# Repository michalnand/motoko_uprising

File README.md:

# Motoko Uprising
## line following robot with neural network predictor

Advanced line following robot, using custom deep neural network for curve shape prediction.
Robot can recognize straight line and speed up.

* Video1 of woking robot [motoko video 1](https://www.youtube.com/watch?v=E9FJIDowNmU)
* Video2 of woking robot [motoko video 2](https://www.youtube.com/watch?v=xUAJ1LA6Xwc)

## hardware

* CPU is ARM Cortex M4F, stm32f303, 72MHz
  * with simd instructions, good to have for deep learning
* gyroscope : lsm303 
  * (or something like THAT - yeah, they are changing it more often then socks)
* motors : pololu HP 1:30, micro metal gear, with magnetic encoders
* motor driver : TI DRV8834
* line sensors : phototransitors for visible light (not IR)
  * Iam using white leds, so the line can be colored - not only black
* obstacle detection :
  * common IR leds, and laser (still not working as I wish - too slow, but high range)
* accu : LiPol 2S, 150mAh, from dualsky

Some photos from mounting this devilry device :
* PCB design are in  [pcb](hardware/export), ready to send to your favorite manufactor
  * 
  * 
  * 
  * 
  
* Chassis, there are little of 3D printed parts [3d print](hardware/chassis)
  * 

## firmware

### control loops

* ADC reads line sensor, using quadratic interpolation for precission line position estimation
* for steering PD controller is used
* for motor controll two PIDs are used (data from encoders are filtered by low pass filters)
* target speed is estimated by neural network, using line shape classification

### neural network

tiny convolutional neural network is used, with architecture :
IN1x8x8 - C4x3x3 - P2x2 - C8x3x3 - P2x2 - FC5

the custom embedded CNN framework is used

```cpp
LineNetwork::LineNetwork()
			:EmbeddedNet()
{
  input_shape.w = 8;
  input_shape.h = 8;
  input_shape.d = 1;

  output_shape.w = 1;
  output_shape.h = 1; 
  output_shape.d = 5;

  layers[0] = new EmbeddedNetConvolutionLayer(layer_0_shape,layer_0_input_shape,layer_0_output_shape,layer_0_weights,layer_0_bias,layer_0_weights_range,layer_0_bias_range);
  layers[1] = new EmbeddedNetMaxPoolingLayer(layer_1_shape,layer_1_input_shape,layer_1_output_shape);
  layers[2] = new EmbeddedNetConvolutionLayer(layer_2_shape,layer_2_input_shape,layer_2_output_shape,layer_2_weights,layer_2_bias,layer_2_weights_range,layer_2_bias_range);
  layers[3] = new EmbeddedNetMaxPoolingLayer(layer_3_shape,layer_3_input_shape,layer_3_output_shape);
  layers[4] = new EmbeddedNetFcLayer(layer_4_shape,layer_4_input_shape,layer_4_output_shape,layer_4_weights,layer_4_bias,layer_4_weights_range,layer_4_bias_range);

  layers_count = 5;
  allocate_buffer();
}
```

### PIDs

PIDs in differential form are used, with antiwindup and derivation kick avoid trick

the controller equation is :
%20%3D%20u(n-1)%20%2B%20k_0e(n)%20%2B%20k_1e(n-1)%20%2B%20k_2e(n-2))

where
* e(n) is error
* u(n) is controller output
* k0 = kp + ki + kd
* k1 = -kp     -2kd
* k2 = kd

```cpp
float PID::process(float error, float plant_output)
{
    e1 = e0;
    e0 = error;

    x2 = x1;
    x1 = x0;
    x0 = plant_output;

    u+= k0*e0 + k1*e1 - kd*(x0 - 2*x1 + x2);

    if (u > limit)
      u = limit;

    if (u < -limit)
      u = -limit;

    return u;
}
```

motors controllers step response :

## debug application

There is debug application written in Python. Data received from robot are visualised in custom GUI written
using OpenGL. Data are transfered in JSON format.

Robot GUI is also designed in json - to modify gui design, only this file need to be modified. Example of gui.json file format : 

```json
"widgets" :
  {
    "type"      : "label",
    "position"  : [0.0, 0.0, 0.0],
    "color"     : [1.0, 0.0, 0.0],
    "font_size" : 0.1,

    "widgets" : [
                  {
                    "type"           : "bar_graph",
                    "position"       : [-2.0, 1.25, 0.0],
                    "color"          : [0.5, 1.0, 0.0],
                    "bar_color"      : [0.8, 0.8, 0.8],

                    "font_size" : 0.05,

                    "width"     : 1.5,
                    "height"    : 0.5,

                    "filled"    : false,
                    "enlight_max_value" : false,

                    "frame_width" : 0.01,
                    "label"     : "LINE SENSORS",

                    "min_value" : 0.0,
                    "max_value" : 1024.0,

                    "variable"  : {
                                    "name"  : "line_sensors",
                                    "value" : [3, 40, 500, 1000, 700, 50, 0, 0]
                                  }
                  },
...
```

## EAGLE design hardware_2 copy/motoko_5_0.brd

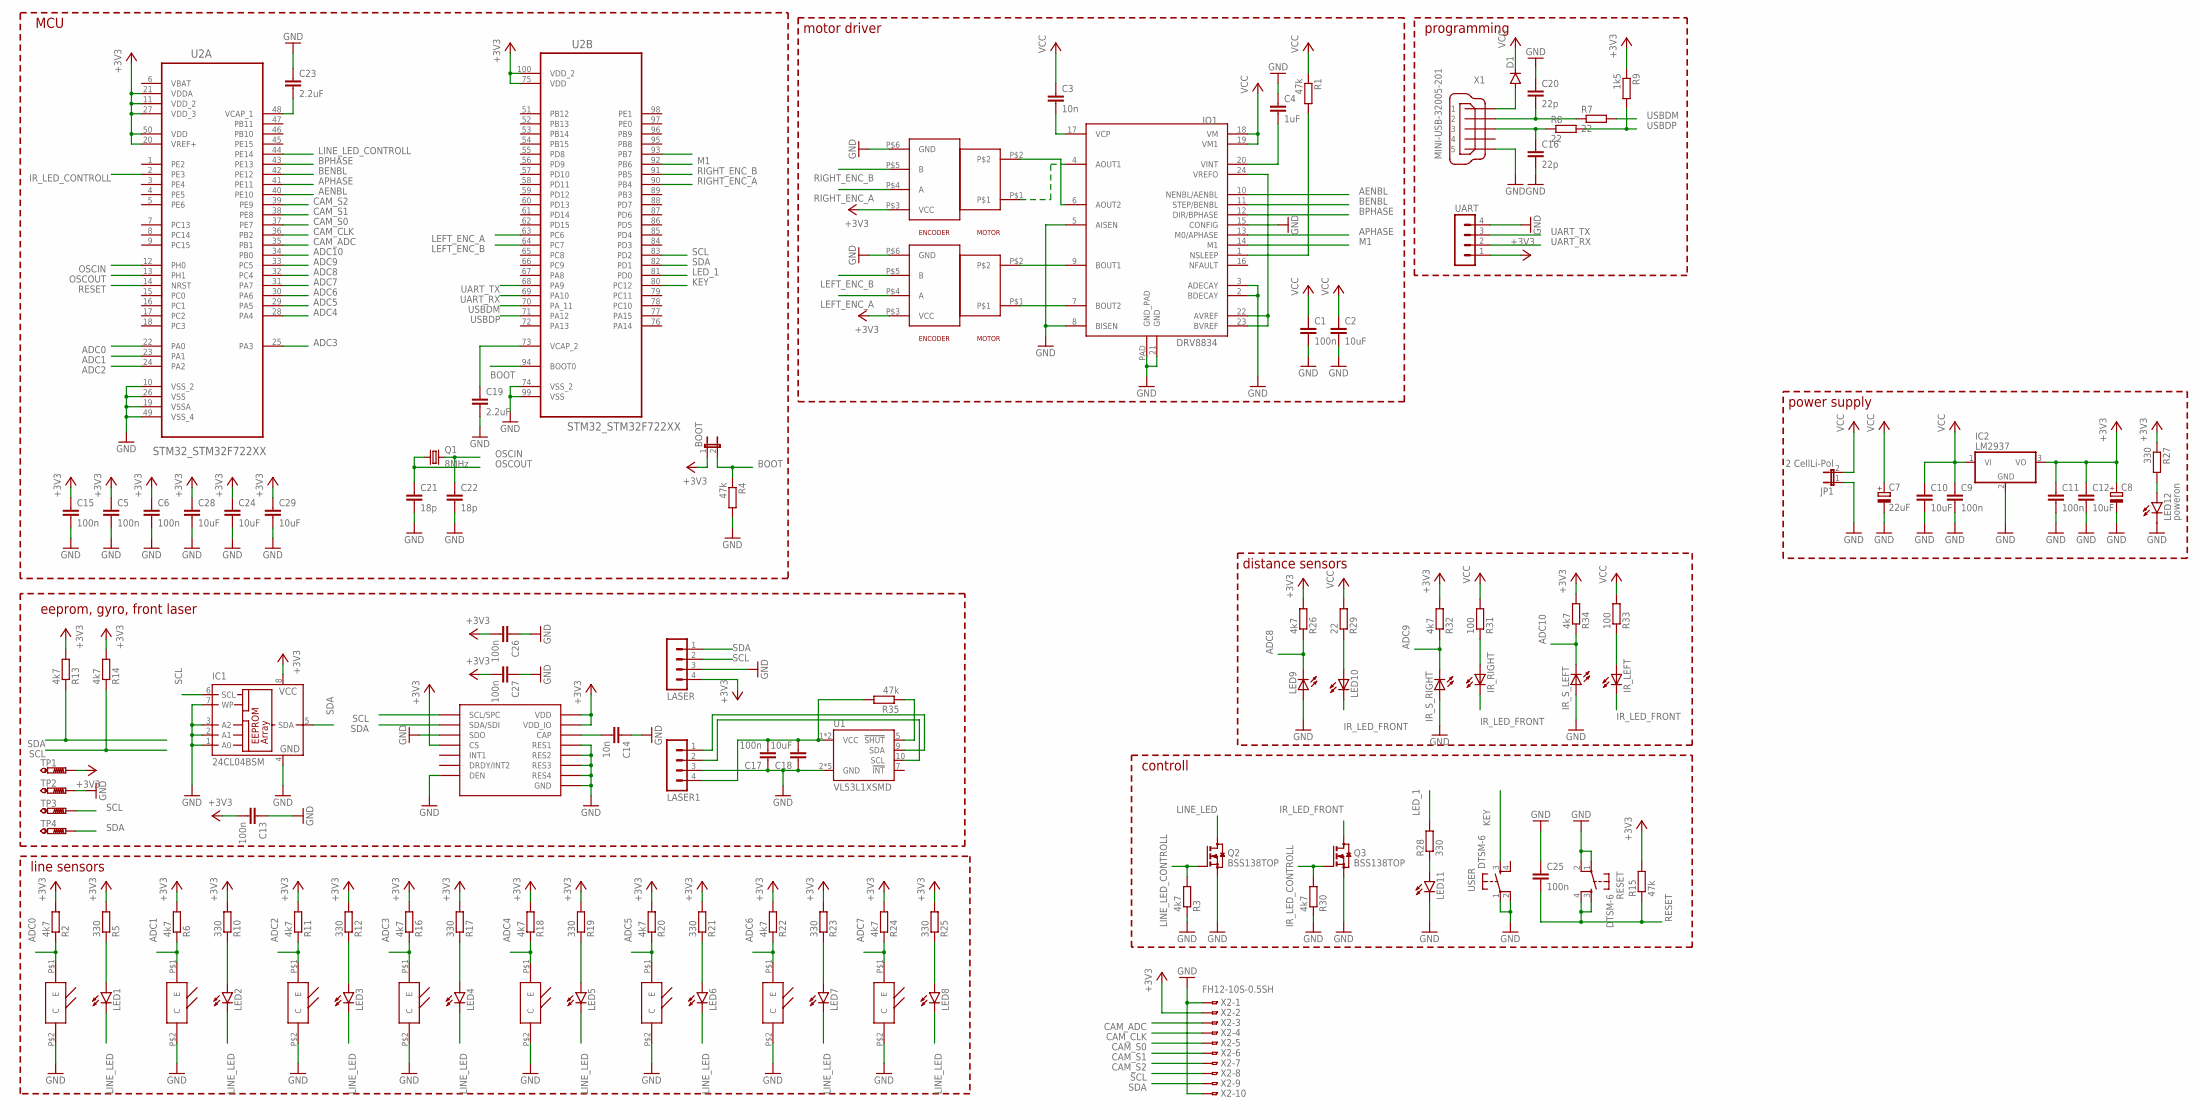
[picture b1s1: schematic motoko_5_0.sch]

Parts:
BOOT: JP1E; JP1
C1: 100n; C1206
C2: 10uF; C1206
C3: 10n; C1206
C4: 1uF; C1206
C5, C6, C9, C11, C13, C15, C17, C25, C26, C27: 100n; C0805
C7: 22uF; 153CLV-0505
C8: CPOL-EU140CLH-1010; 140CLH-1010
C10, C12, C18, C24, C28, C29: 10uF; C0805
C14: 10n; C0805
C16, C20: 22p; C0805
C19, C23: 2.2uF; C0805
C21, C22: 18p; C0805
D1: DIODE-SMB; SMB
IC1: 24CL04BSM; SO-08M
IC2: LM2937; TO263-3
IO1: DRV8834; DRV8834_PCK
IR_LEFT: LED5MM
IR_RIGHT: LED5MM
IR_S_LEFT: LED5MM
IR_S_RIGHT: LED5MM
JP1: 2 CellLi-Pol; JP1
LASER, LASER1: MA04-1
LED1, LED2, LED3, LED4, LED5, LED6, LED7, LED8, LED11: LEDCHIPLED_1206; CHIPLED_1206
LED9, LED10: LED5MM
LED12: poweron; CHIPLED_1206
LSM6DS0: ST_L3GD20H; ST_LGA16L
Q1: 8MHz; CTS406
Q2, Q3: BSS138TOP; SOT23
R1: 47k; M1206
R2, R3, R6, R11, R13, R14, R16, R18, R20, R22, R24, R26, R30, R32, R34: 4k7; M0805
R4, R15, R35: 47k; M0805
R5, R10, R12, R17, R19, R21, R23, R25, R27, R28: 330; M0805
R7, R8, R29: 22; M0805
R9: 1k5; M0805
R31, R33: 100; M0805
RESET: DTSM-6
TP1, TP2, TP3, TP4: PTR1B1,27; B1,27
U1: VL53L1XSMD; VL53L1X
U2: STM32_STM32F722XX; STM32_QFP50P1600X1600X160-100N
U$3, U$4, U$5, U$6, U$7, U$8, U$9, U$10: SFH3710
U$11, U$12: POLOLU_GEAR_MOTORPOLO; POLOLU_GEAR_MOTOR
UART: MA04-1
USER: DTSM-6
X1: MINI-USB-32005-201; 32005-201
X2: FH12-10S-0.5SH

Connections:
+3V3: BOOT.1, C5.1, C6.1, C8.+, C11.1, C12.1, C13.2, C15.1, C24.1, C26.2, C27.2, C28.1, C29.1, IC1.8 (VCC), IC2.3 (VO), LASER.4, LSM6DS0.P$1 (VDD_IO), LSM6DS0.P$5 (CS), LSM6DS0.P$16 (VDD), R2.2, R5.2, R6.2, R9.1, R10.2, R11.2, R12.2, R13.2, R14.2, R15.2, R16.2, R17.2, R18.2, R19.2, R20.2, R21.2, R22.2, R23.2, R24.2, R25.2, R26.2, R27.1, R32.2, R34.2, TP1.TP, U2.11 (VDD_2), U2.20 (VREF+), U2.21 (VDDA), U2.27 (VDD_3), U2.50 (VDD), U2.75 (VDD), U2.100 (VDD_2), U$11.P$3 (VCC), U$12.P$3 (VCC), UART.1, X2.2
ADC0: R2.1, U2.22 (PA0), U$3.P$1 (E)
ADC1: R6.1, U2.23 (PA1), U$4.P$1 (E)
ADC2: R11.1, U2.24 (PA2), U$5.P$1 (E)
ADC3: R16.1, U2.25 (PA3), U$6.P$1 (E)
ADC4: R18.1, U2.28 (PA4), U$7.P$1 (E)
ADC5: R20.1, U2.29 (PA5), U$8.P$1 (E)
ADC6: R22.1, U2.30 (PA6), U$9.P$1 (E)
ADC7: R24.1, U2.31 (PA7), U$10.P$1 (E)
ADC8: LED9.K (C), R26.1, U2.32 (PC4)
ADC9: IR_S_RIGHT.K (C), R32.1, U2.33 (PC5)
ADC10: IR_S_LEFT.K (C), R34.1, U2.34 (PB0)
AENBL: IO1.10 (NENBL/AENBL), U2.40 (PE10)
APHASE: IO1.13 (M0/APHASE), U2.41 (PE11)
BENBL: IO1.11 (STEP/BENBL), U2.42 (PE12)
BOOT: BOOT.2, R4.1, U2.94 (BOOT0)
BPHASE: IO1.12 (DIR/BPHASE), U2.43 (PE13)
CAM_ADC: U2.35 (PB1), X2.3
CAM_CLK: U2.36 (PB2), X2.4
CAM_S0: U2.37 (PE7), X2.5
CAM_S1: U2.38 (PE8), X2.6
CAM_S2: U2.39 (PE9), X2.7
GND: C1.2, C2.2, C4.1, C5.2, C6.2, C7.-, C8.-, C9.2, C10.2, C11.2, C12.2, C13.1, C14.1, C15.2, C16.2, C17.1, C18.1, C19.2, C20.1, C21.2, C22.2, C23.1, C24.2, C25.1, C26.1, C27.1, C28.2, C29.2, IC1.1 (A0), IC1.2 (A1), IC1.3 (A2), IC1.4 (GND), IC1.7 (WP), IC2.2 (GND), IO1.2 (BDECAY), IO1.3 (ADECAY), IO1.5 (AISEN), IO1.8 (BISEN), IO1.15 (CONFIG), IO1.21 (GND), IO1.PAD (GND_PAD), IR_S_LEFT.A, IR_S_RIGHT.A, JP1.1, LASER.3, LASER1.3, LED9.A, LED11.C, LED12.C, LSM6DS0.P$4 (SDO), LSM6DS0.P$8 (DEN), LSM6DS0.P$9 (RES1), LSM6DS0.P$10 (RES2), LSM6DS0.P$11 (RES3), LSM6DS0.P$12 (GND), LSM6DS0.P$13 (GND), LSM6DS0.P$15 (RES4), Q2.2 (S), Q3.2 (S), R3.1, R4.2, R30.1, RESET.1, RESET.2, TP2.TP, U1.2 (GND), U1.3 (GND), U1.4 (GND), U1.6 (GND), U1.12 (GND), U2.10 (VSS_2), U2.19 (VSSA), U2.26 (VSS), U2.49 (VSS_4), U2.74 (VSS_2), U2.99 (VSS), U$3.P$2 (C), U$4.P$2 (C), U$5.P$2 (C), U$6.P$2 (C), U$7.P$2 (C), U$8.P$2 (C), U$9.P$2 (C), U$10.P$2 (C), U$11.P$6 (GND), U$12.P$6 (GND), UART.4, USER.1, USER.2, X1.5, X2.1, X2.10
IR_LED_CONTROLL: Q3.1 (G), R30.2, U2.2 (PE3)
IR_LED_FRONT: IR_LEFT.K (C), IR_RIGHT.K (C), LED10.K (C), Q3.3 (D)
KEY: U2.80 (PC12), USER.3
LED_1: R28.2, U2.81 (PD0)
LEFT_ENC_A: U2.63 (PC6), U$11.P$4 (A)
LEFT_ENC_B: U2.64 (PC7), U$11.P$5 (B)
LINE_LED: LED1.C, LED2.C, LED3.C, LED4.C, LED5.C, LED6.C, LED7.C, LED8.C, Q2.3 (D)
LINE_LED_CONTROLL: Q2.1 (G), R3.2, U2.44 (PE14)
M1: IO1.14 (M1), U2.92 (PB6)
unnamed: IO1.6 (AOUT2), U$12.P$2
unnamed: IO1.4 (AOUT1), U$12.P$1
unnamed: IO1.7 (BOUT2), U$11.P$1
unnamed: IO1.9 (BOUT1), U$11.P$2
unnamed: C3.2, IO1.17 (VCP)
unnamed: C14.2, LSM6DS0.P$14 (CAP)
unnamed: LED10.A, R29.1
unnamed: IO1.22 (AVREF), IO1.23 (BVREF), IO1.24 (VREFO)
unnamed: IO1.1 (NSLEEP), R1.2
unnamed: IR_LEFT.A, R33.1
unnamed: LED1.A, R5.1
unnamed: LED2.A, R10.1
unnamed: LED3.A, R12.1
unnamed: LED4.A, R17.1
unnamed: LED5.A, R19.1
unnamed: LED6.A, R21.1
unnamed: LED7.A, R23.1
unnamed: LED8.A, R25.1
unnamed: C4.2, IO1.20 (VINT)
unnamed: LED12.A, R27.2
unnamed: IR_RIGHT.A, R31.1
unnamed: C19.1, U2.73 (VCAP_2)
unnamed: C17.2, C18.2, LASER1.4, R35.2, U1.1 (VCC), U1.11 (VCC)
unnamed: LASER1.1, U1.9 (SDA)
unnamed: LASER1.2, U1.10 (SCL)
unnamed: R35.1, U1.5 (!SHUT)
unnamed: C23.2, U2.48 (VCAP_1)
unnamed: LED11.A, R28.1
unnamed: C20.2, R7.1, X1.2
unnamed: C16.1, R8.1, X1.3
unnamed: D1.A, X1.1
OSCIN: C22.1, Q1.3 (2), U2.12 (PH0)
OSCOUT: C21.1, Q1.1, U2.13 (PH1)
RESET: C25.2, R15.1, RESET.3, RESET.4, U2.14 (NRST)
RIGHT_ENC_A: U2.90 (PB4), U$12.P$4 (A)
RIGHT_ENC_B: U2.91 (PB5), U$12.P$5 (B)
SCL: IC1.6 (SCL), LASER.2, LSM6DS0.P$2 (SCL/SPC), R14.1, TP3.TP, U2.83 (PD2), X2.8
SDA: IC1.5 (SDA), LASER.1, LSM6DS0.P$3 (SDA/SDI), R13.1, TP4.TP, U2.82 (PD1), X2.9
UART_RX: U2.69 (PA10), UART.2
UART_TX: U2.68 (PA9), UART.3
USBDM: R7.2, U2.70 (PA_11)
USBDP: R8.2, R9.2, U2.71 (PA12)
VBAT: U2.6 (VBAT)
VCC: C1.1, C2.1, C3.1, C7.+, C9.1, C10.1, D1.C, IC2.1 (VI), IO1.18 (VM), IO1.19 (VM1), JP1.2, R1.1, R29.2, R31.2, R33.2

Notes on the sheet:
power supply
line sensors
programming
MCU
motor driver
distance sensors
controll
eeprom, gyro, front laser

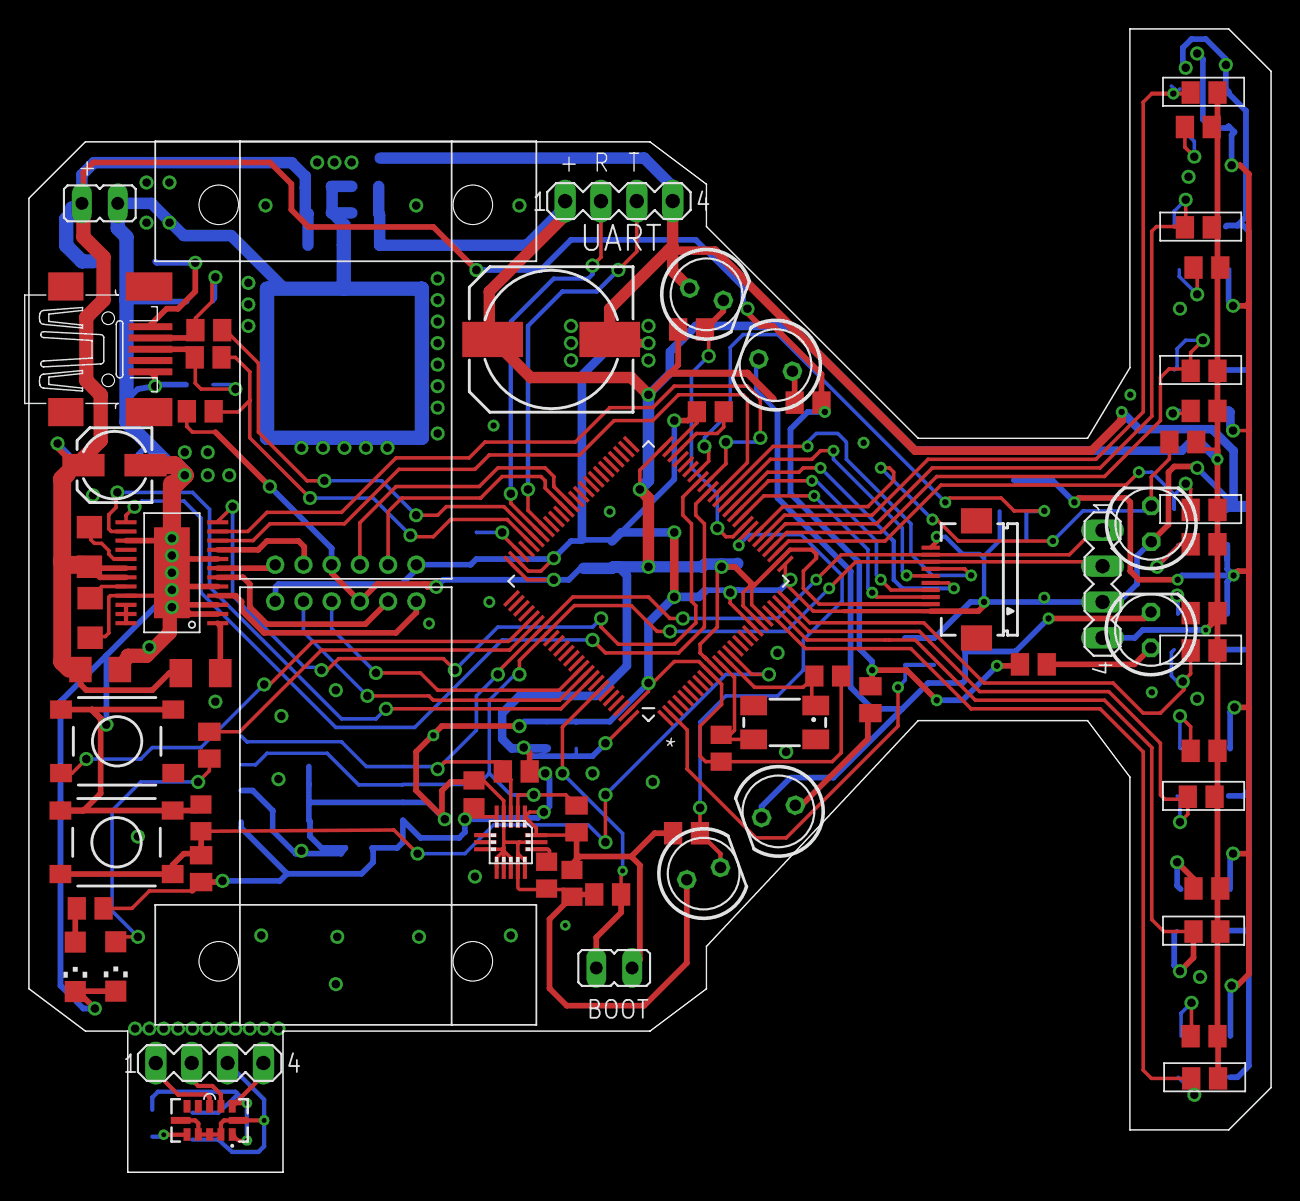
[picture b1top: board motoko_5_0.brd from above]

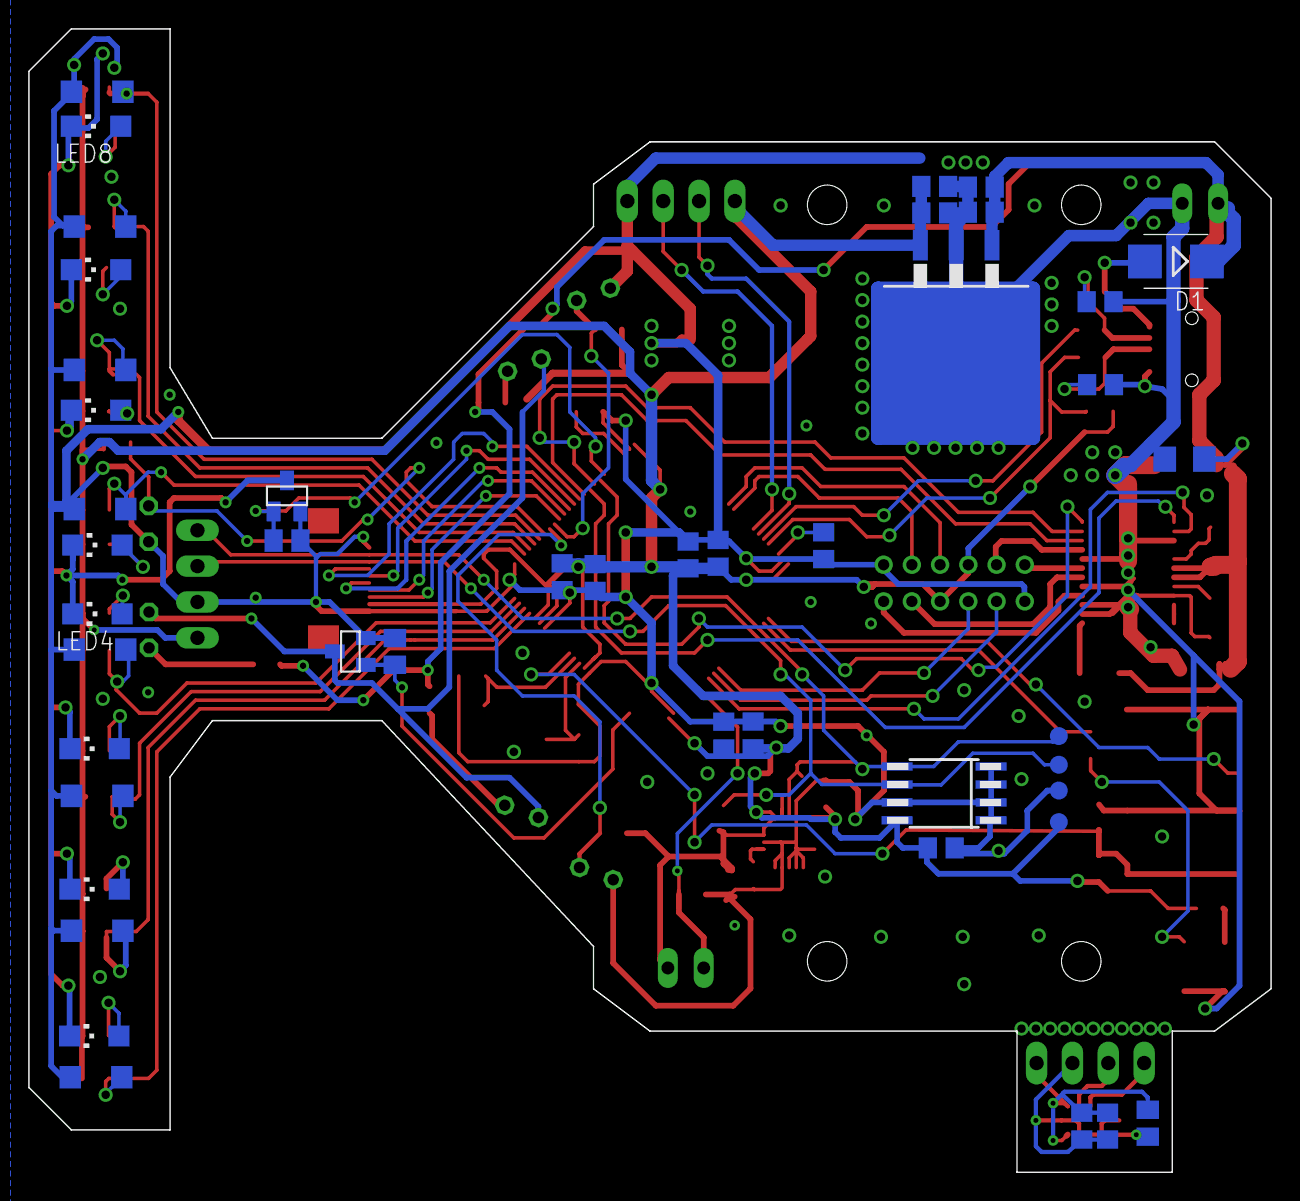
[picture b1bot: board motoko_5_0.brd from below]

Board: 2 copper layers, 88.0 x 81.0 mm, 113 parts (45 on the bottom side), 75 nets.

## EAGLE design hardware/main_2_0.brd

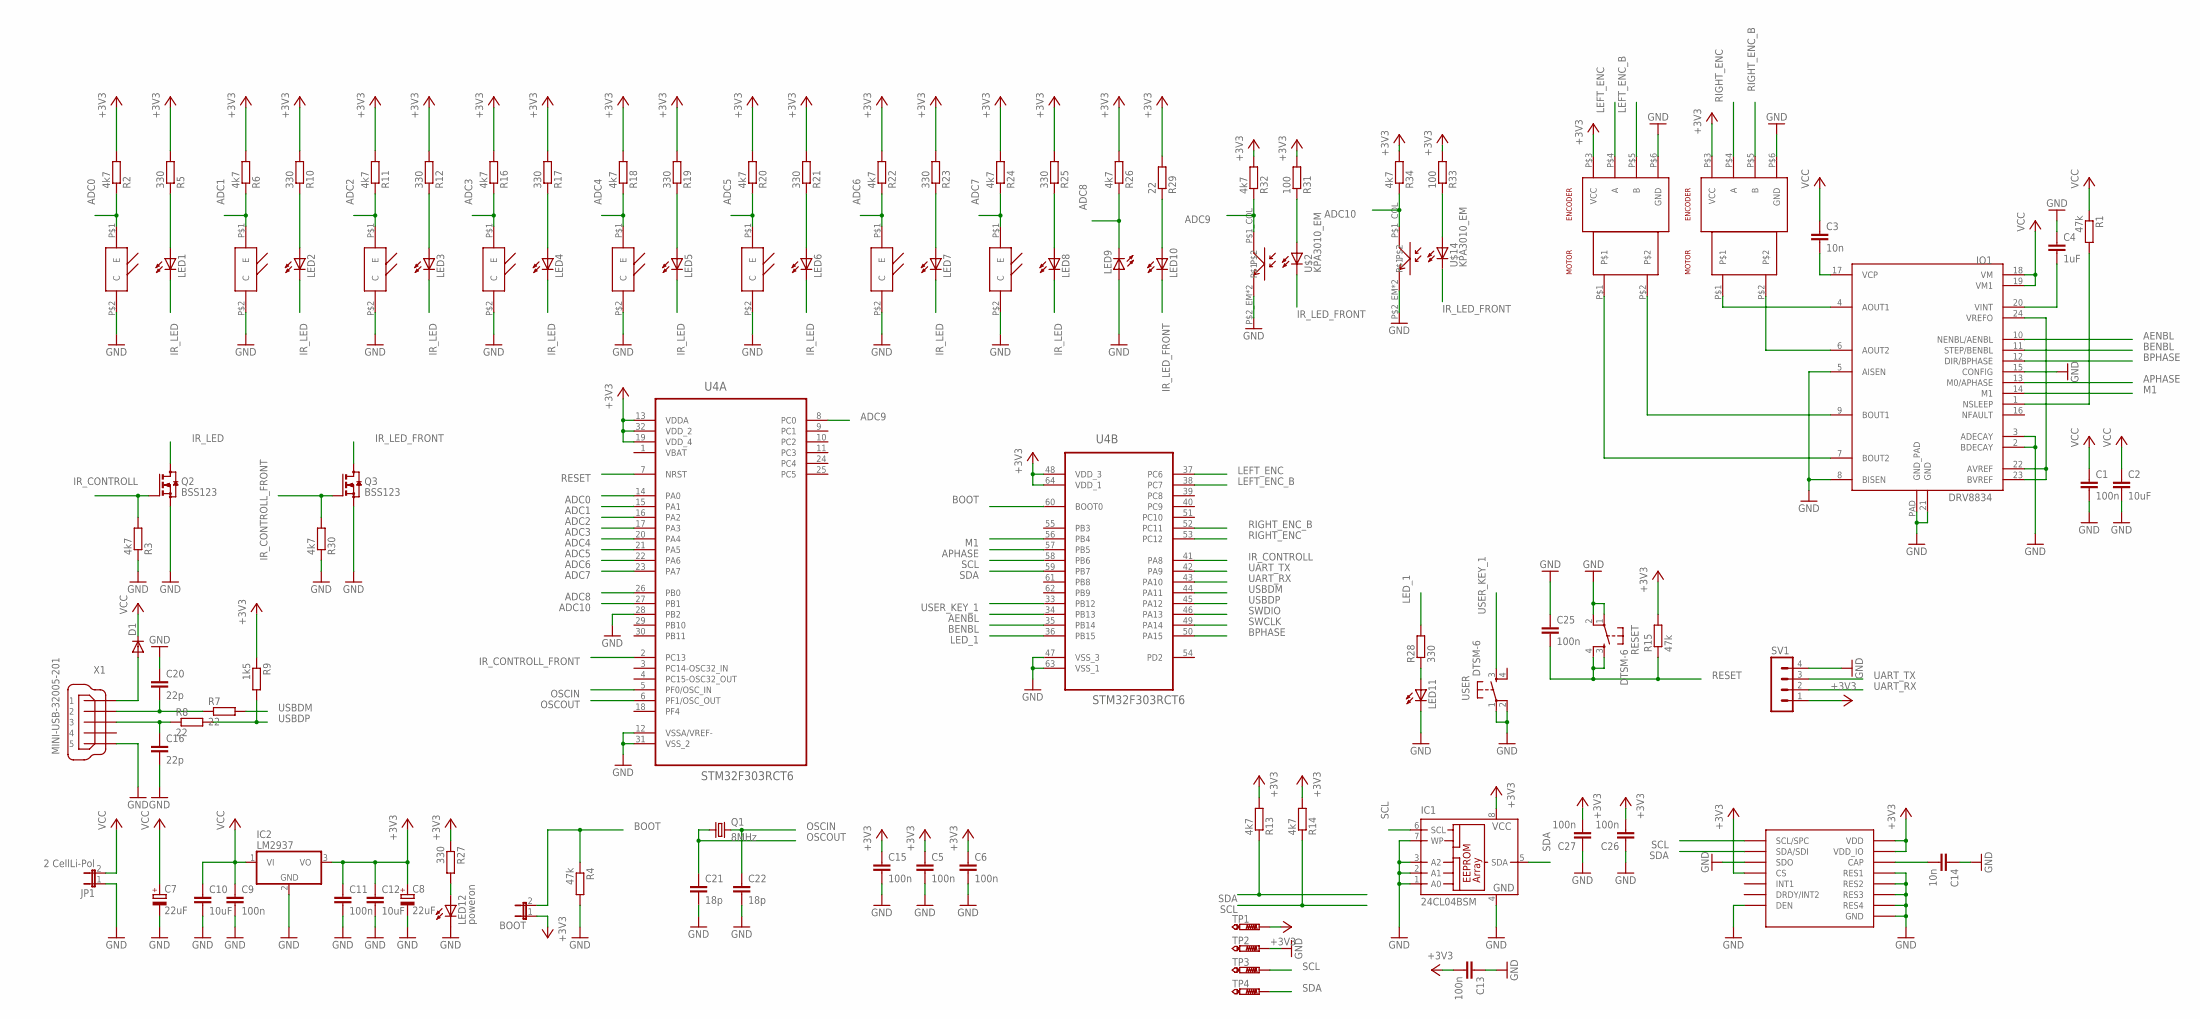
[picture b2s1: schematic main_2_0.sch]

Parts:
BOOT: JP1E; JP1
C1: 100n; C1206
C2: 10uF; C1206
C3: 10n; C1206
C4: 1uF; C1206
C5, C6, C9, C11, C13, C15, C25, C26, C27: 100n; C0805
C7, C8: 22uF; 153CLV-0505
C10, C12: 10uF; C0805
C14: 10n; C0805
C16, C20: 22p; C0805
C21, C22: 18p; C0805
D1: DIODE-SMB; SMB
IC1: 24CL04BSM; SO-08M
IC2: LM2937; TO263-3
IO1: DRV8834; DRV8834_PCK
JP1: 2 CellLi-Pol; JP1
LED1, LED2, LED3, LED4, LED5, LED6, LED7, LED8, LED11: LEDCHIPLED_1206; CHIPLED_1206
LED9, LED10: LED5MM
LED12: poweron; CHIPLED_1206
LSM6DS0: L3GD20H; LGA16L
Q1: 8MHz; CTS406
Q2, Q3: BSS123; SOT23
R1: 47k; M1206
R2, R3, R6, R11, R13, R14, R16, R18, R20, R22, R24, R26, R30, R32, R34: 4k7; M0805
R4, R15: 47k; M0805
R5, R10, R12, R17, R19, R21, R23, R25, R27, R28: 330; M0805
R7, R8, R29: 22; M0805
R9: 1k5; M0805
R31, R33: 100; M0805
RESET: DTSM-6
SV1: MA04-1
TP1, TP2, TP3, TP4: PTR1B1,27; B1,27
U4: STM32F303RCT6; QFP50P1200X1200X160-64N
U$1, U$13: KPA3010
U$2, U$14: KPA3010_EM; KPA3010
U$3, U$4, U$5, U$6, U$7, U$8, U$9, U$10: SFH3710
U$11, U$12: POLOLU_GEAR_MOTORPOLO; POLOLU_GEAR_MOTOR
USER: DTSM-6
X1: MINI-USB-32005-201; 32005-201

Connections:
+3V3: BOOT.1, C5.1, C6.1, C8.+, C11.1, C12.1, C13.2, C15.1, C26.2, C27.2, IC1.8 (VCC), IC2.3 (VO), LSM6DS0.P$1 (VDD_IO), LSM6DS0.P$5 (CS), LSM6DS0.P$16 (VDD), R2.2, R5.2, R6.2, R9.1, R10.2, R11.2, R12.2, R13.2, R14.2, R15.2, R16.2, R17.2, R18.2, R19.2, R20.2, R21.2, R22.2, R23.2, R24.2, R25.2, R26.2, R27.1, R29.2, R31.2, R32.2, R33.2, R34.2, SV1.1, TP1.TP, U4.13 (VDDA), U4.19 (VDD_4), U4.32 (VDD_2), U4.48 (VDD_3), U4.64 (VDD_1), U$11.P$3 (VCC), U$12.P$3 (VCC)
ADC0: R2.1, U4.14 (PA0), U$3.P$1 (E)
ADC1: R6.1, U4.15 (PA1), U$4.P$1 (E)
ADC2: R11.1, U4.16 (PA2), U$5.P$1 (E)
ADC3: R16.1, U4.17 (PA3), U$6.P$1 (E)
ADC4: R18.1, U4.20 (PA4), U$7.P$1 (E)
ADC5: R20.1, U4.21 (PA5), U$8.P$1 (E)
ADC6: R22.1, U4.22 (PA6), U$9.P$1 (E)
ADC7: R24.1, U4.23 (PA7), U$10.P$1 (E)
ADC8: LED9.K (C), R26.1, U4.26 (PB0)
ADC9: R32.1, U4.8 (PC0), U$1.P$1_COL
ADC10: R34.1, U4.27 (PB1), U$13.P$1_COL
AENBL: IO1.10 (NENBL/AENBL), U4.34 (PB13)
APHASE: IO1.13 (M0/APHASE), U4.57 (PB5)
BENBL: IO1.11 (STEP/BENBL), U4.35 (PB14)
BOOT: BOOT.2, R4.1, U4.60 (BOOT0)
BPHASE: IO1.12 (DIR/BPHASE), U4.50 (PA15)
GND: C1.2, C2.2, C4.1, C5.2, C6.2, C7.-, C8.-, C9.2, C10.2, C11.2, C12.2, C13.1, C14.1, C15.2, C16.2, C20.1, C21.2, C22.2, C25.1, C26.1, C27.1, IC1.1 (A0), IC1.2 (A1), IC1.3 (A2), IC1.4 (GND), IC1.7 (WP), IC2.2 (GND), IO1.2 (BDECAY), IO1.3 (ADECAY), IO1.5 (AISEN), IO1.8 (BISEN), IO1.15 (CONFIG), IO1.21 (GND), IO1.PAD (GND_PAD), JP1.1, LED9.A, LED11.C, LED12.C, LSM6DS0.P$4 (SDO), LSM6DS0.P$8 (DEN), LSM6DS0.P$9 (RES1), LSM6DS0.P$10 (RES2), LSM6DS0.P$11 (RES3), LSM6DS0.P$12 (GND), LSM6DS0.P$13 (GND), LSM6DS0.P$15 (RES4), Q2.2 (S), Q3.2 (S), R3.1, R4.2, R30.1, RESET.1, RESET.2, SV1.4, TP2.TP, U4.12 (VSSA/VREF-), U4.28 (PB2), U4.31 (VSS_2), U4.47 (VSS_3), U4.63 (VSS_1), U$1.P$2_EM, U$1.P$3-NC, U$3.P$2 (C), U$4.P$2 (C), U$5.P$2 (C), U$6.P$2 (C), U$7.P$2 (C), U$8.P$2 (C), U$9.P$2 (C), U$10.P$2 (C), U$11.P$6 (GND), U$12.P$6 (GND), U$13.P$2_EM, U$13.P$3-NC, USER.1, USER.2, X1.5
IR_CONTROLL: Q2.1 (G), R3.2, U4.41 (PA8)
IR_CONTROLL_FRONT: Q3.1 (G), R30.2, U4.2 (PC13)
IR_LED: LED1.C, LED2.C, LED3.C, LED4.C, LED5.C, LED6.C, LED7.C, LED8.C, Q2.3 (D)
IR_LED_FRONT: LED10.K (C), Q3.3 (D), U$2.P$1_COL (C), U$14.P$1_COL (C)
LED_1: R28.2, U4.36 (PB15)
LEFT_ENC: U4.37 (PC6), U$11.P$4 (A)
LEFT_ENC_B: U4.38 (PC7), U$11.P$5 (B)
M1: IO1.14 (M1), U4.56 (PB4)
unnamed: IO1.6 (AOUT2), U$12.P$2
unnamed: IO1.4 (AOUT1), U$12.P$1
unnamed: IO1.7 (BOUT2), U$11.P$1
unnamed: IO1.9 (BOUT1), U$11.P$2
unnamed: C3.2, IO1.17 (VCP)
unnamed: C14.2, LSM6DS0.P$14 (CAP)
unnamed: LED10.A, R29.1
unnamed: IO1.22 (AVREF), IO1.23 (BVREF), IO1.24 (VREFO)
unnamed: IO1.1 (NSLEEP), R1.2
unnamed: R33.1, U$14.P$2_EM (A), U$14.P$3-NC (A)
unnamed: LED1.A, R5.1
unnamed: LED2.A, R10.1
unnamed: LED3.A, R12.1
unnamed: LED4.A, R17.1
unnamed: LED5.A, R19.1
unnamed: LED6.A, R21.1
unnamed: LED7.A, R23.1
unnamed: LED8.A, R25.1
unnamed: C4.2, IO1.20 (VINT)
unnamed: LED12.A, R27.2
unnamed: R31.1, U$2.P$2_EM (A), U$2.P$3-NC (A)
unnamed: LED11.A, R28.1
unnamed: C20.2, R7.1, X1.2
unnamed: C16.1, R8.1, X1.3
unnamed: D1.A, X1.1
OSCIN: C22.1, Q1.3 (2), U4.5 (PF0/OSC_IN)
OSCOUT: C21.1, Q1.1, U4.6 (PF1/OSC_OUT)
RESET: C25.2, R15.1, RESET.3, RESET.4, U4.7 (NRST)
RIGHT_ENC: U4.53 (PC12), U$12.P$4 (A)
RIGHT_ENC_B: U4.52 (PC11), U$12.P$5 (B)
SCL: IC1.6 (SCL), LSM6DS0.P$2 (SCL/SPC), R14.1, TP3.TP, U4.58 (PB6)
SDA: IC1.5 (SDA), LSM6DS0.P$3 (SDA/SDI), R13.1, TP4.TP, U4.59 (PB7)
SWCLK: U4.49 (PA14)
SWDIO: U4.46 (PA13)
UART_RX: SV1.2, U4.43 (PA10)
UART_TX: SV1.3, U4.42 (PA9)
USBDM: R7.2, U4.44 (PA11)
USBDP: R8.2, R9.2, U4.45 (PA12)
USER_KEY_1: U4.33 (PB12), USER.3
VBAT: U4.1 (VBAT)
VCC: C1.1, C2.1, C3.1, C7.+, C9.1, C10.1, D1.C, IC2.1 (VI), IO1.18 (VM), IO1.19 (VM1), JP1.2, R1.1

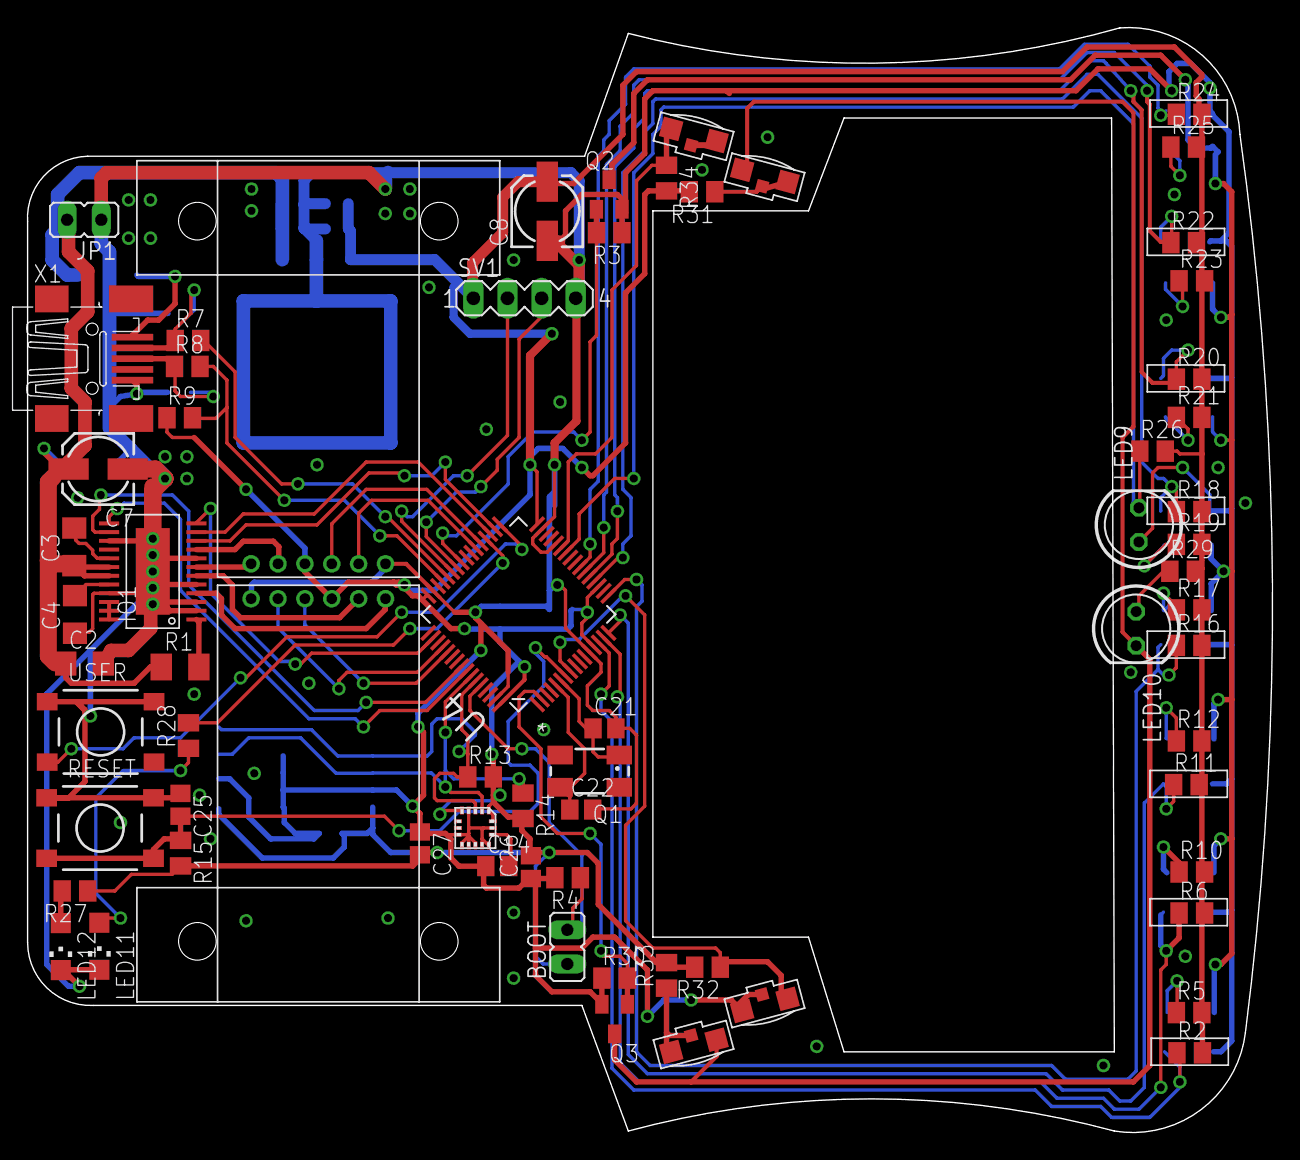
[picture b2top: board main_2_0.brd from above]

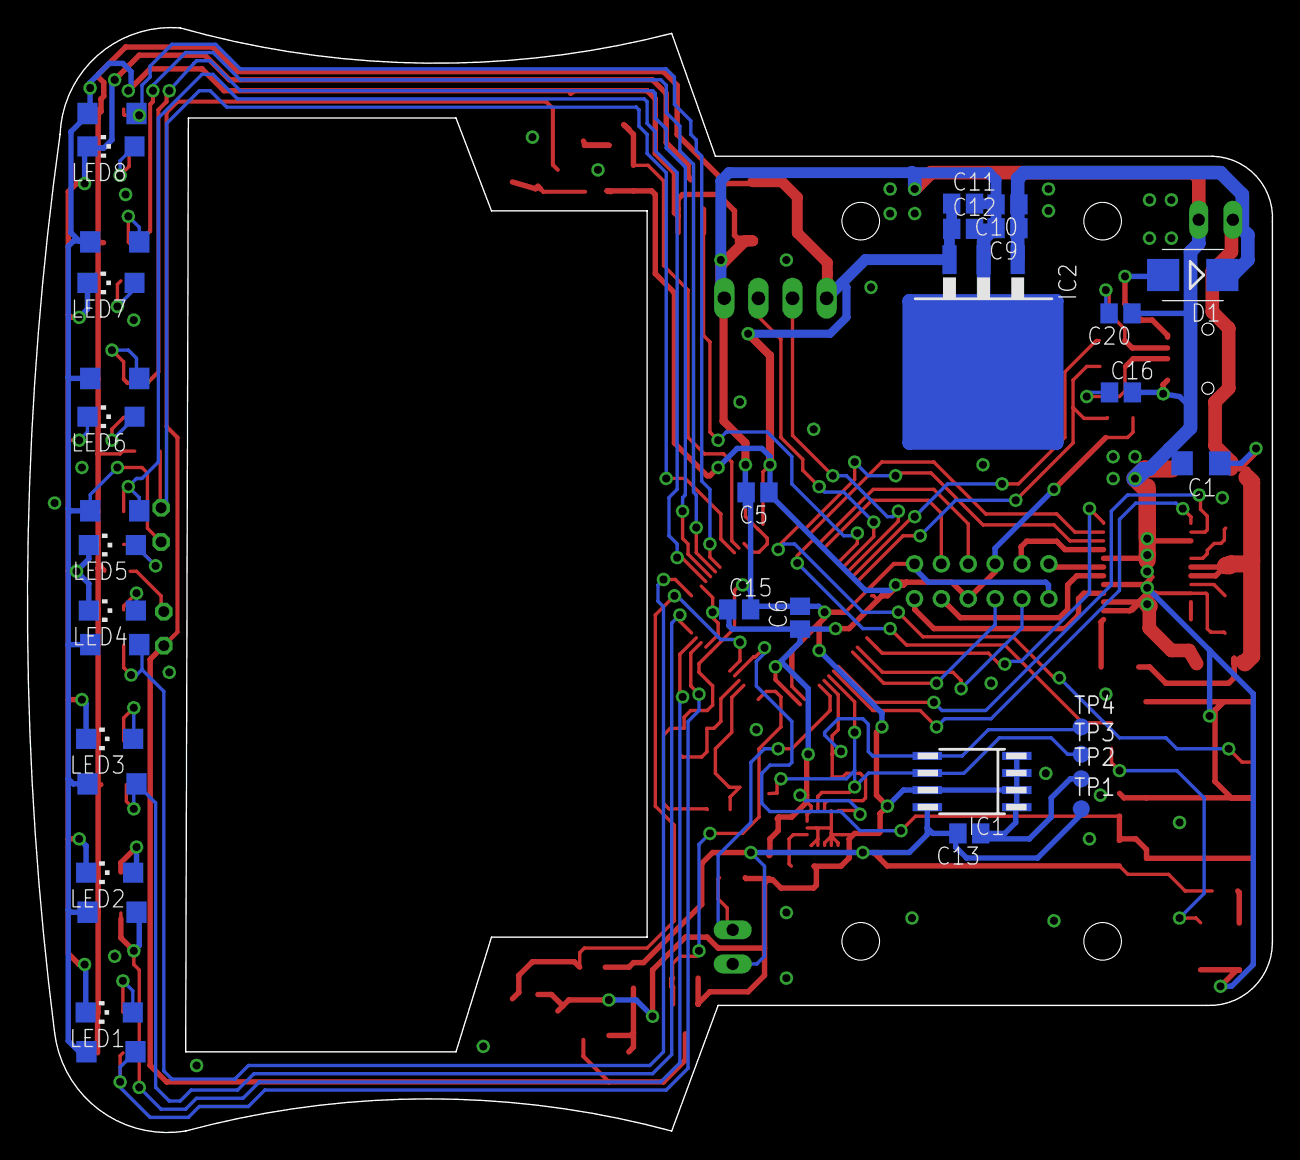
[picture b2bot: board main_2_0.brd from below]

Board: 2 copper layers, 92.6 x 82.2 mm, 101 parts (34 on the bottom side), 64 nets.

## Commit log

2018-09-04 initial
2018-09-05 init code
2018-09-06 initial testing code
2018-09-06 initial drivers test
2018-09-07 motor driver
2018-09-08 motor controll - not tested yet
2018-09-08 motor controll
2018-09-12 code cleaned up
2018-09-13 line follower test
2018-09-13 dense cnn
2018-09-15 common
2018-09-15 nets
2018-09-23 debug app - gui
2018-09-24 robot gui
2018-09-25 debug gui
2018-09-26 debug ap
2018-10-12 line network
2018-12-23 source cleaned up
2018-12-23 line search started
2019-02-07 faster line search
2019-03-17 faster nn
2019-03-24 new network
2019-03-26 network test
2019-04-04 spot
2019-04-11 brick detection
2019-04-12 working code - sometimes
2019-04-20 filter + eeprom
2019-04-24 fine tunning
2019-04-27 new line sensor driver
2019-04-28 new gui
2019-04-28 json map
2019-05-05 line scan camera tests
2019-05-09 line net
2019-05-17 line scan camera net
2019-05-29 tunned code
2019-06-01 prague
2019-06-04 new board
2019-06-07 board
2019-06-11 line search
2019-06-11 cleaned up
2019-06-21 board v4
2019-06-25 bom + board outline
2019-06-25 laser test
2019-06-27 network train
2019-06-27 embedded network
2019-06-27 network
2019-06-28 new network for line following
2019-07-12 new gyro tests
2019-07-19 gyro tests
2019-07-31 new firmware
2019-08-01 movement
2019-11-16 images
2019-11-20 readme
2020-01-18 presentation
2020-04-14 visualisation python
2020-04-16 robot debug
2020-04-17 robot debug app
2021-03-13 new hardware

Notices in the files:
parts and their libraries:
SparkFun-Sensors: Licensing: Creative Commons ShareAlike 4.0 International - https://creativecommons.org/licenses/by-sa/4.0
